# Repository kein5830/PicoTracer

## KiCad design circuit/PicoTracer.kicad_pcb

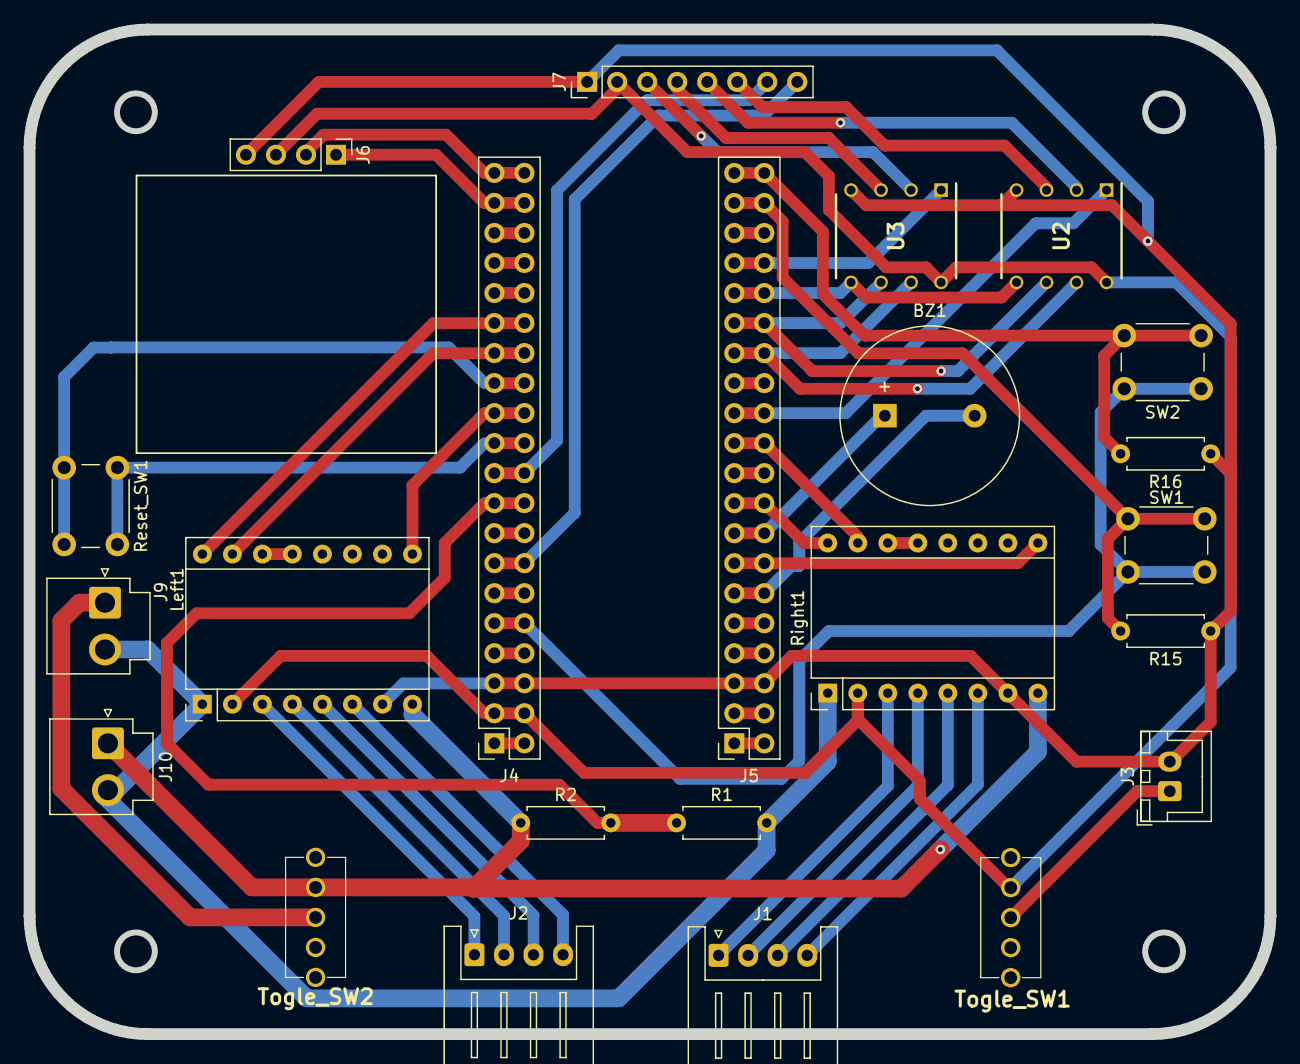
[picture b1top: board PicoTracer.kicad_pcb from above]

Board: 2 copper layers, 105.0 x 85.0 mm, 23 parts (0 on the bottom side), 57 nets.

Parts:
BZ1: Buzzer; Buzzer_15x7.5RM7.6
J1, J2: Conn_01x04_Socket; JST_XH_S4B-XH-A_1x04_P2.50mm_Horizontal
J3: Conn_01x02_Socket; JST_XH_B2B-XH-A_1x02_P2.50mm_Vertical
J4, J5: Conn_02x20_Top_Bottom; PinSocket_2x20_P2.54mm_Vertical_Raspipico
J6: Conn_01x04_Socket; PinHeader_1x04_P2.54mm_Vertical
J7: 8P8C; PinHeader_1x08_P2.54mm_Vertical
J9, J10: Conn_01x02_Socket; JST_VH_B2P-VH_1x02_P3.96mm_Vertical
Left1: Pololu_Breakout_A4988; Pololu_Breakout-16_15.2x20.3mm
R1, R15, R16: 5.1kΩ; R_Axial_DIN0207_L6.3mm_D2.5mm_P7.62mm_Horizontal
R2: 1.0kΩ; R_Axial_DIN0207_L6.3mm_D2.5mm_P7.62mm_Horizontal
Reset_SW1: SW_Push; SW_PUSH_6mm_H4.3mm
Right1: Pololu_Breakout_A4988; Pololu_Breakout-16_15.2x20.3mm
SW1, SW2: SW_Push; SW_PUSH_6mm_H4.3mm
Togle_SW1, Togle_SW2: SW_SPDT; 2MS1T1B4VS2QES
U2, U3: MCP3002; DIP781W56P254L950H533Q8N

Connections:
3.3V: J4.5, J4.25, SW1.2, SW2.1
+5V: J3.1, Togle_SW1.2 (B)
+12V: J9.1, Togle_SW2.2 (B)
Clock: J5.14, J5.34, U2.7 (CLK), U3.7 (CLK)
Curve_Sensor: J4.7, J4.27, J7.8
Din: J5.16, J5.36, U2.5 (DIN), U3.5 (DIN)
Dout: J5.15, J5.35, U2.6 (DOUT), U3.6 (DOUT)
GND_5V: J3.2, J4.3, J4.23, J5.3, J5.23, J6.4, J7.1, Left1.7 (GND), R15.1, R16.1, Right1.7 (GND), U2.4 (VSS), U3.4 (VSS)
GND_12V: J9.2, J10.2, Left1.1 (GND), R1.2, Right1.1 (GND)
Goal_Sensor: J4.10, J4.30, J7.7
Left_Direction: J4.15, J4.35, Left1.16 (DIR)
Left_Enable: J4.12, J4.32, Left1.9 (~ENABLE)
Left_Step: J4.14, J4.34, Left1.15 (STEP)
unnamed: BZ1.1 (+), J5.8, J5.28
unnamed: BZ1.2 (-), J5.6, J5.26
unnamed: J1.1, Right1.3 (1B)
unnamed: J1.2, Right1.4 (1A)
unnamed: J1.3, Right1.5 (2A)
unnamed: J1.4, Right1.6 (2B)
unnamed: J2.1, Left1.3 (1B)
unnamed: J2.2, Left1.4 (1A)
unnamed: J2.3, Left1.5 (2A)
unnamed: J2.4, Left1.6 (2B)
unnamed: J4.1, J4.21
unnamed: J4.2, J4.22, J6.3, J7.2, Left1.2 (VDD), Right1.2 (VDD), Togle_SW1.1 (A), U2.8 (VDD/VREF), U3.8 (VDD/VREF)
unnamed: J4.11, J4.31, Reset_SW1.1
unnamed: J4.13, J4.33, Reset_SW1.2
unnamed: J4.16, J4.36
unnamed: J4.17, J4.37
unnamed: J4.18, J4.38
unnamed: J4.19, J4.39, J6.1
unnamed: J4.20, J4.40, J6.2
unnamed: J4.4, J4.24
unnamed: J4.6, J4.26
unnamed: J4.8, J4.28
unnamed: J4.9, J4.29, R1.1, R2.2
unnamed: J5.1, J5.21
unnamed: J5.2, J5.22
unnamed: J5.10, J5.30
unnamed: J5.13, J5.33
unnamed: J5.18, J5.38
unnamed: J5.19, J5.39, R15.2, SW1.1
unnamed: J5.20, J5.40, R16.2, SW2.2
unnamed: J5.4, J5.24
unnamed: J5.5, J5.25
unnamed: J10.1, Left1.8 (VMOT), R2.1, Right1.8 (VMOT), Togle_SW2.1 (A)
unnamed: Left1.13 (~RESET), Left1.14 (~SLEEP)
unnamed: Right1.13 (~RESET), Right1.14 (~SLEEP)
unnamed: J7.5, U2.2 (CH0)
unnamed: J7.6, U2.3 (CH1)
unnamed: J7.3, U3.2 (CH0)
unnamed: J7.4, U3.3 (CH1)
Right_Direction: J5.9, J5.29, Right1.16 (DIR)
Right_Enable: J5.7, J5.27, Right1.9 (~ENABLE)
Right_Step: J5.11, J5.31, Right1.15 (STEP)
Sel1: J5.12, J5.32, U2.1 (~CS/SHDN)
Sel2: J5.17, J5.37, U3.1 (~CS/SHDN)

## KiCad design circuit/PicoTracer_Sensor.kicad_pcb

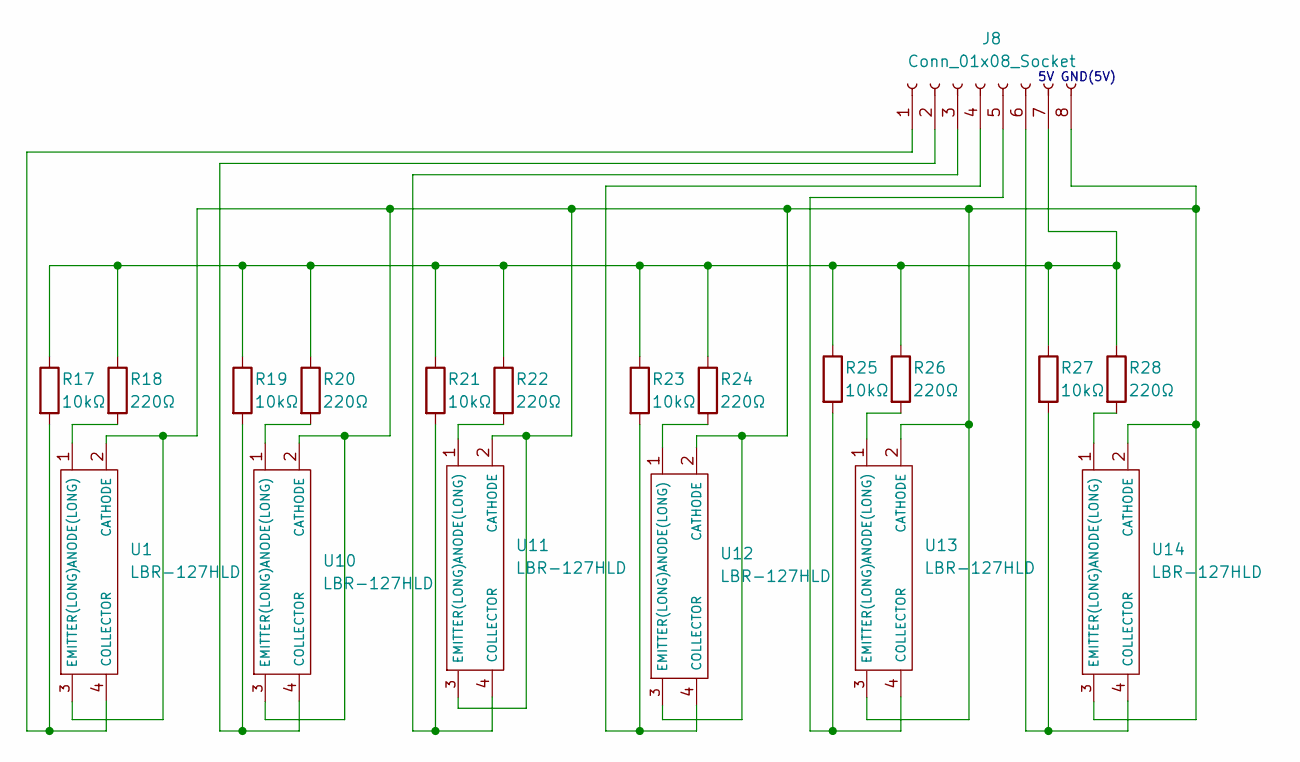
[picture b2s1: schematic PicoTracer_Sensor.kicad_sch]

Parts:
J8: Conn_01x08_Socket; PinSocket_1x08_P2.54mm_Vertical
R17, R19, R21, R23, R25, R27: 10kΩ; R_Axial_DIN0207_L6.3mm_D2.5mm_P7.62mm_Horizontal
R18, R20, R22, R24, R26, R28: 220Ω; R_Axial_DIN0207_L6.3mm_D2.5mm_P7.62mm_Horizontal
U1, U10, U11, U12, U13, U14: LBR-127HLD; LBR127HLD; Manufacturer_Part_Number LBR-127HLD

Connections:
unnamed: J8.1, R17.2, U1.4 (COLLECTOR)
unnamed: J8.2, R19.2, U10.4 (COLLECTOR)
unnamed: J8.3, R21.2, U11.4 (COLLECTOR)
unnamed: J8.4, R23.2, U12.4 (COLLECTOR)
unnamed: J8.5, R25.2, U13.4 (COLLECTOR)
unnamed: J8.6, R27.2, U14.4 (COLLECTOR)
unnamed: J8.7, R17.1, R18.1, R19.1, R20.1, R21.1, R22.1, R23.1, R24.1, R25.1, R26.1, R27.1, R28.1
unnamed: J8.8, U1.2 (CATHODE), U1.3 (EMITTER(LONG)), U10.2 (CATHODE), U10.3 (EMITTER(LONG)), U11.2 (CATHODE), U11.3 (EMITTER(LONG)), U12.2 (CATHODE), U12.3 (EMITTER(LONG)), U13.2 (CATHODE), U13.3 (EMITTER(LONG)), U14.2 (CATHODE), U14.3 (EMITTER(LONG))
unnamed: R18.2, U1.1 (ANODE(LONG))
unnamed: R20.2, U10.1 (ANODE(LONG))
unnamed: R22.2, U11.1 (ANODE(LONG))
unnamed: R24.2, U12.1 (ANODE(LONG))
unnamed: R26.2, U13.1 (ANODE(LONG))
unnamed: R28.2, U14.1 (ANODE(LONG))

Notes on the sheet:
GND(5V)

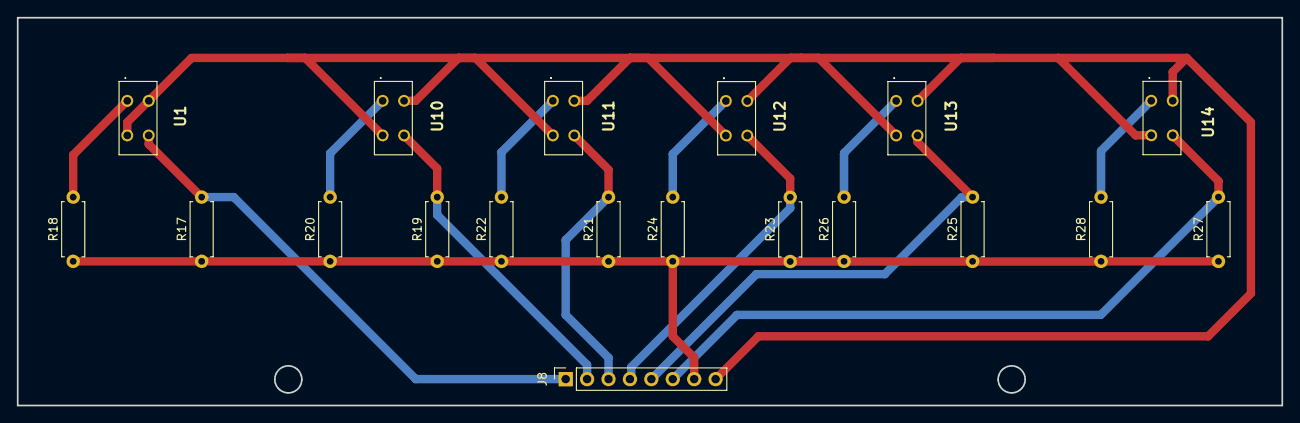
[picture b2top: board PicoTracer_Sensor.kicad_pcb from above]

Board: 2 copper layers, 150.0 x 46.0 mm, 19 parts (0 on the bottom side), 14 nets.

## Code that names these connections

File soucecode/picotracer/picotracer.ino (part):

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//AD変換ピン
#define SELPIN1 9    //前後どっちか確認する
#define SELPIN2 13   //前後どっちか確認する
#define DATAOUT 12   //mcp3002:DOUT---pico:GP12(SPI1 RX)
#define DATAIN 11    //mcp3002:DIN---pico:GP11(SPI1 TX)
#define SPICLOCK 10  //Clock
#define GOALSENSOR 28
#define Curve_Sensor 26
#define ch0 0
#define ch1 1

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
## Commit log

2024-01-31 高速化調整：P制御＋PI制御、Pゲイン、PIゲイン調整&速度の高速化
2024-02-02 PCBデータ初回コミット
2024-02-08 Update picotracer.ino コメント追加
2024-02-15 現状不明一旦統一
2024-02-17 ファイル復帰
2024-02-17 フォルダ名変更
2024-02-17 backupあれこれ（変更なし）
2024-02-19 タイマー２つ動かしたScene4
2024-02-20 Scene4にて加速プログラム
2024-02-20 void setupにてPWMを使ったモーター制御プログラム記載（途中）
2024-02-21 wrap値とパルス周波数の関係、Duty比についてをコメントに追加、functionにwrapとパルス周波数を変換する関数追加
2024-03-02 走行終了時に再度モード選択ができるように修正（未完成）
2024-03-02 走行終了時に再度モード選択ができるように修正
2024-03-31 kicadファイル更新 部品配置
2024-03-31 部品リスト更新
2024-04-10 ・A4988の配線追加
2024-04-14 ・スイッチ配線 ・AD変換器電源以外の配線完了
2024-05-20 scene5に電圧計測追加
2024-05-23 抵抗値コメント追記
2024-05-26 電源周り追加、プッシュスイッチ追加、電圧計測回路追加、センサー回路追加
2024-05-26 * 電源周り追加、プッシュスイッチ追加、電圧計測回路追加、センサー回路追加
2024-06-02 pullup用抵抗を追加（未試験のため検証して動きに問題なければつなぐ）
2024-06-03 プッシュスイッチにPullup抵抗を追加
2024-06-28 回路図いったん完成、PCBファイルに基盤外形追加
2024-08-08 回路図：完成、配線図：配置のみ完了
2024-08-09 バージョン8.0に更新
2024-08-09 配線途中
2024-08-09 mac内kicad更新のため
2024-08-17 配線図完成、回路図スイッチの配線位置変更
2024-08-24 ・配線完了
2024-09-09 ・メイン基板 最終版
2024-09-09 sensor基盤回路図：完成、配線図：部品配置まで
2024-09-09 配線図：配線まで完了 ガーバーファイル出すときに水色の線を出さないよう注意！
2024-09-17 配膳図、回路図の追加
2024-09-24 ピン割り当て変更
2024-09-25 ブザーを鳴らすためのtone関数追加
2024-09-29 ブザー鳴らす処理追加
2024-09-29 SSD1306表示コード実装
2024-10-01 電圧読み取り、表示部更新（未チェック）
2024-10-01 デバッグ用Serialprint追加
2024-10-06 ・電圧測定計算追加
2024-10-14 ・Scene5のコードをモーター、センサーのテスト用に修正
2024-10-15 ・コメントなど一部修正
2024-10-20 ・ADコンバータのピン番号修正、センサー配置の修正
2024-10-22 ・コード共有のため
2024-10-30 九州大会調整結果＆ずれによるセンサー値の変化を計測するソースコード追加（scene5）
2024-11-11 code share 一旦虚っゆう
2024-11-11 PicoTracer-backupsファイルを管理外に変更 センサー、メイン配線図ファイル修正、その他ファイル更新
2024-11-18 現状コード共有 センサー値を配列に保存する仕組みのj検証中
2024-11-19 update/コメント修正（途中）、関数削除
    関数などのコメントをわかりやすいように統一（途中 完了次第再コミット）
    必要ないScene6の削除とscene5を完全にコメントアウト
2024-11-20 update/コメント修正(完了)、一部変数名の変更\n関数のコメントを統一
2024-11-24 update:コメント修正、待機モード中の処理を定周期処理＋イベント処理に変更
    ・変数の説明などのコメントを見やすいよう修正
    ・プッシュスイッチ待機、ディスプレイ更新、バッテリー電圧取得処理を、loop()へのべた書きからmillis()を使った定周期処理に変更
2024-12-01 update/実行モード中のWhileLoop廃止、コメント修正
    ・ディスプレイ表示部のコメントを削除
    ・実行モード時に、ディスプレイ更新、電圧取得関数を定周期実行しないように変更
    ・実行関数のWhileLoopを廃止して、メインLoopで実行するように修正。それに伴い、終了時に待機モードに移行するように修正
    ・ディスプレイのモード表示が２つから４つに増えるに伴い、引数をboolから、uint8_tに変更
    ・switch case 内に実行関数を登録していないものも追加し、ディスプレイに「No Action」と表示するよう変更
    ・0~9以外の番号が入力さ
2024-12-01 ブランチを枝分かれさせるため用
2024-12-01 fix/PWM停止忘れによるバグ修正、Reset()内の処理修正、Scene4用変数をグローバル変数に変更、実行中のsw1を無効化
    ・各Sceneにより、PWMを開始した後に、待機モードに遷移し、Scene5以降の入っていないSceneに遷移した場合に以前のSceneのPWMが実行されたままで、モーターが回ってしまうバグの修正
    ・Reset()内の、Run=0という処理を削除
    ・Scene４のSpeed変数をグローバル変数に変更し、リセット時に加速したスピードをリセットできるように修正
    ・実行中にsw1を押すことで、Sceneが切り替わってしまうバグを修正
2024-12-02 fix/Scene3でリセットがかからないバグ修正、update/実行モードを定周期実行に変更、Scene2～４の加速を＋１ずつに変更、関数のコメントの修正
    ・Scene3において終了時にリセット関数を入れていないことによるバグ修正（Reset()の追加）
    ・実行モードのswitch caseを定周期実行に変更（現在は10ms周期 遅延はなさげ）
    ・PWM関数の引数がuint16の型なのに対して、floatの値を入れることにより、動作がおかしい部分が存在していたため、小数点での加速を廃止し、＋１に統一→今後は別の仕組みで加速制御の実装を予定
    ・関数のコ
2024-12-08 基盤ファイルをgit管理しないよう変更
2024-12-08 基盤ファイルをgit管理から削除
2024-12-15 add:ログ用構造体の定義
    ・ログ取得用構造体を定義
    ・定周期ごとに値を取得する関数の定義（途中）
2024-12-19 update/types.hファイル追加、ログ保存用構造体作成、Scene５でシリアルプリントによるログ出力
    ・ログ保存機能を追加したかったが、シリアル出力までしかできず、Flashへの保存機能は未実装
    ・ブザー変更によるtone関数の追加
    ・バッテリー電圧測定の計算値を変更
2025-02-04 update/一部Sceneの古いセンサの入力配置修正
    一部Sceneの古いセンサの入力配置を修正（chとSELPIN1,2）
    大会時に考えていた内容についてコメント追記
2025-02-04 fix/謎の全角スペースを削除\n\n謎の全角スペースが混入しておりコンパイルが通らなかったため修正
2025-02-15 update:取得項目削減＆ログ一時保存用配列サイズ変更、Flashメモリ書き込み処理（途中）
    3分間ログを保存できるように配列サイズを10000 -> 18500に変更 10ms周期なら185秒保存可能
    RAMサイズ上モーター出力値は取得しない（PIDの計算から求めることは可能）
    Flashメモリに書き込む処理を追加しようとしたが、大会までの残り時間上途中
2025-02-15 fix:USB電源の際にAD変換器、ディスプレイの初期設定を無効化 update:buzzerが周波数によって音階を変化するように修正
    USB電源でマイコンを動作させている時にAD変換器のHIGH出力により3.3Vラインに2Vほど電圧がかかることがあり、その処置（3.3Vを入れて入れば問題なし）
    ブザーを変更したためarduinoのtone関数を利用
2025-02-15 update:センサー回路変更によるAD変換器引数の修正
    AD変換器のchとCSピン配置修正
2025-02-15 update:Scene５にセンサー値チェック用関数追加、イベント処理のScene番号遷移処理修正
    Scene５にセンサー値をSerialprintに出力する処理を追加
    Scene番号遷移のイベントを待機モード中にしか遷移させないように修正
    それに伴い、実行モード中のSW1スイッチを検知できるように修正（もともとはScene番号が実行中に遷移しないように無効化していた）
2025-02-15 fix:あるSceneを実行した後に、別のSceneを実行すると前のSceneが残っている問題の修正
    あるSceneを実行し、停止した時にPWMの出力を停止しているはずだが、待機中もオンになっており、実行時にモーター電源をオンにした時に一瞬動いてしまう
    →待機中ずっとPWMをOFFにする処理を実行
2025-02-15 update:スタート、ゴール時にブザーを追加、センサー反応時にもコメントアウトしているが追加
    ブザー音追加 センサー反応時にも追加したが、モーターがうるさすぎて聞こえないのでいったんコメントアウト状態にしている。
2025-02-16 Update:左右センサーの合計値をPID制御する仕様に変更 ゲインの調整 センサー値のバイアスを追加
    ログ取得ブランチをマージするために一時的にコミット
2025-03-09 update:Scene1,Scene2全日本変更
    updata:速度、ゲイン、センサーごとの誤差調整
    updata:マーカー検知センサー値の調整
    updata:ログ保存用構造体の拡張、センサー値以外の値を取れるように型の修正
    updata:Scene1,Scene2の速度変更
2025-03-16 fix:Hzwrap()のWrap値上限の設定
    Wrap値がuint16の上限を超えないよう修正
2025-04-07 update:micros()を使用したモータ動作システムの導入、距離計測関数追加
    picotracer.inoにmicros()から一定周期で関数を呼び出す仕組みを作成し、パルスを生成する仕組みの導入（定周期実行処理と同じ）
    function.inoに上記処理によって求められるステップ数から距離を計算する関数を追加
2025-04-17 ・テストコミット Gitのテストのため、コメントを追加し変更した。 実際に変更を加えるときに削除する。
2025-05-18 update:Scene2,3コメントアウト、Curveマーカー用センサー値取得変数の名前修正、Curveマーカー検知機能追加(Scene0)、モーター回転用の周期変数名変更
    前回のupdate分：距離取得関数追加
    今回のupdate分：
    Scene2、３ 一旦使用しないためコメントアウト
    Curveマーカーセンサ値を保存する変数名を変更 Curve -> sensorCurve
    Curveマーカー検知機能を追加 ただしクロスラインとの切り分け方法を次のバージョンで修正するため、この部分も修正する予定
    モーター回転用の周期変数名変更 interval1 -> intervalR interval2 -> intervalL
2025-06-08 ・update：スタートからの距離計測機能、ゴールとカーブマーカのカウント方法変更、コメント修正
    距離計測機能：実行モードに遷移してから、10msごとにGet_Distance()を実行し、距離を取得する。NowDistanceを一時変数に保存することで、その地点からの距離を取得できる、はず。
    ゴール、カーブマーカ取得方法変更：これまでは、マーカセンサでのカウント値からクロス分を引く方法だったが、クロスを検知したら、35mmはクロスフラグをONにし、その間にマーカセンサが反応してもカウントしないように変更
2025-06-09 update:関数のファイル分割
    関数の持つ機能ごとにファイルを分け見やすくした。
    詳細onenoteの「関数ファイル分け」ページ参照
2025-06-29 update:Scene0にマーカごとの距離取得機能を追加、その他コメントの修正など
    Scene0にスタートからゴールまでの各マーカー間の距離をmarker_distance[]に記録する機能を追加（配列は100個までなので、コースによってはオーバーする可能性あり）
    Logにマーカのカウントなどを出力するように修正
2025-11-09 add/加速テーブル追加
    ・加減速走行実装のため、加速テーブルを追加（加速テーブルはマイクロマウスサンプルを参考に作成）
2025-11-09 update/Scene4：テスト用のモータ動作の変更Scene5：不要部分の削除やみたい変数の追加などScene6：無効化部分の解除
    ・Scene4：モーターの動作を加速テーブルをベースにした制御に変更したため、それの対応を実施
    ・Scene5：センサー試験において必要ない処理の削除とみたい変数の追加
    ・Scene6：ログ出力機能のコメント解除とログ出力中にモーターが回転しないような処理の追加
2025-11-09 update/制御方式変更による基準速度の変更、ゴールマーカ検知後の動作変更、不要コメントの削除など
    ・ゴールマーカ検知後にタイマー割り込みで時間で止めていたものから、マーカー検知後に速度0まで減速する処理に変更
2025-11-09 add/マーカを元に加減速走行する機能の実装、不要コメントの削除など
    ・１走目でカーブマーカ間の走行距離を取得し、２走目のマーカー間で1000mm以上の距離であれば、加減速を実施するように処理
2025-11-09 add/センサー値の正規化の動作確認処理追加
    ・センサー値の正規化処理が動作しているか試すために処理を追加したが、走行では使用していない
2025-11-09 add/Scene1の加減速走行をコピーし、マーカー間の距離を手打ちで追加したモード
    ・加減速走行の練習のために追加（本番では使用せず）
2025-11-09 update/バッテリー電圧更新、プッシュスイッチの検知、走行距離計測機能を、メインループの擬似タイマー処理から、タイマー割り込み関数に移動
    ・もともとメインループで擬似タイマー割り込みして実装していた機能をタイマー割り込み関数を使用した処理に変更、それにより走行時にタイマーの停止、リセット時にタイマーを再開する処理を追加
2025-11-09 update/タイマー処理の追加、必要な変数の追加、モーター制御方法の変更、定周期処理の変更など
    ・定周期処理で追加していたバッテリー電圧計測、プッシュスイッチ検知、走行距離計測機能をタイマーライブラリに移動
